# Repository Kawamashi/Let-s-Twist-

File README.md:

# Let's Twist !
## Ergonomic split mechanical keyboard

I'm an [Ergodox keyboard](https://www.ergodox.io/) user. Even if I'm really happy with it, there's room for improvement. *Let's Twist !* is an attempt to gather every brilliant idea I've seen on other ergonomic split keyboards.

First of all, I want to keep some of the Ergodox features :
- the thumb clusters, because it's a great way to lighten the work of the other fingers.
- the columnar staggered arrangement of the keys, because it's way more natural than the traditional row staggered layout.
- the split design, because it allows you to have a very comfortable position.
- programmable with QMK, I don't think I need to explain why…
- 1.5u wide keys on the outer columns, because it's aesthetically pleasing ! 
- wired connectivity, because I don't like to rely on batteries, and because I like my custom cables !

Then, like a lot of people, I find that the thumb clusters of the Ergodox are too far away from the alphas. I saw Mikel Duffy's great [modified Ergodox](https://medium.com/@mikelduffy/hand-wiring-a-modified-ergodox-1adbfc479468), and I want the two main thumb keys to be in the same position.

My project was heavily inspired by Mattia Dal Ben's [Redox keyboard](https://github.com/mattdibi/redox-keyboard). It's really a stunning project. Like him, I want my keyboard to have a reduced size, and to be able to plug either half (or just one of them) to the PC. 

So, here is the layout I get :

The PCB can manage 2 or 3 keys for each of the thumb clusters. The blue keys can be 1u or 1.25u.

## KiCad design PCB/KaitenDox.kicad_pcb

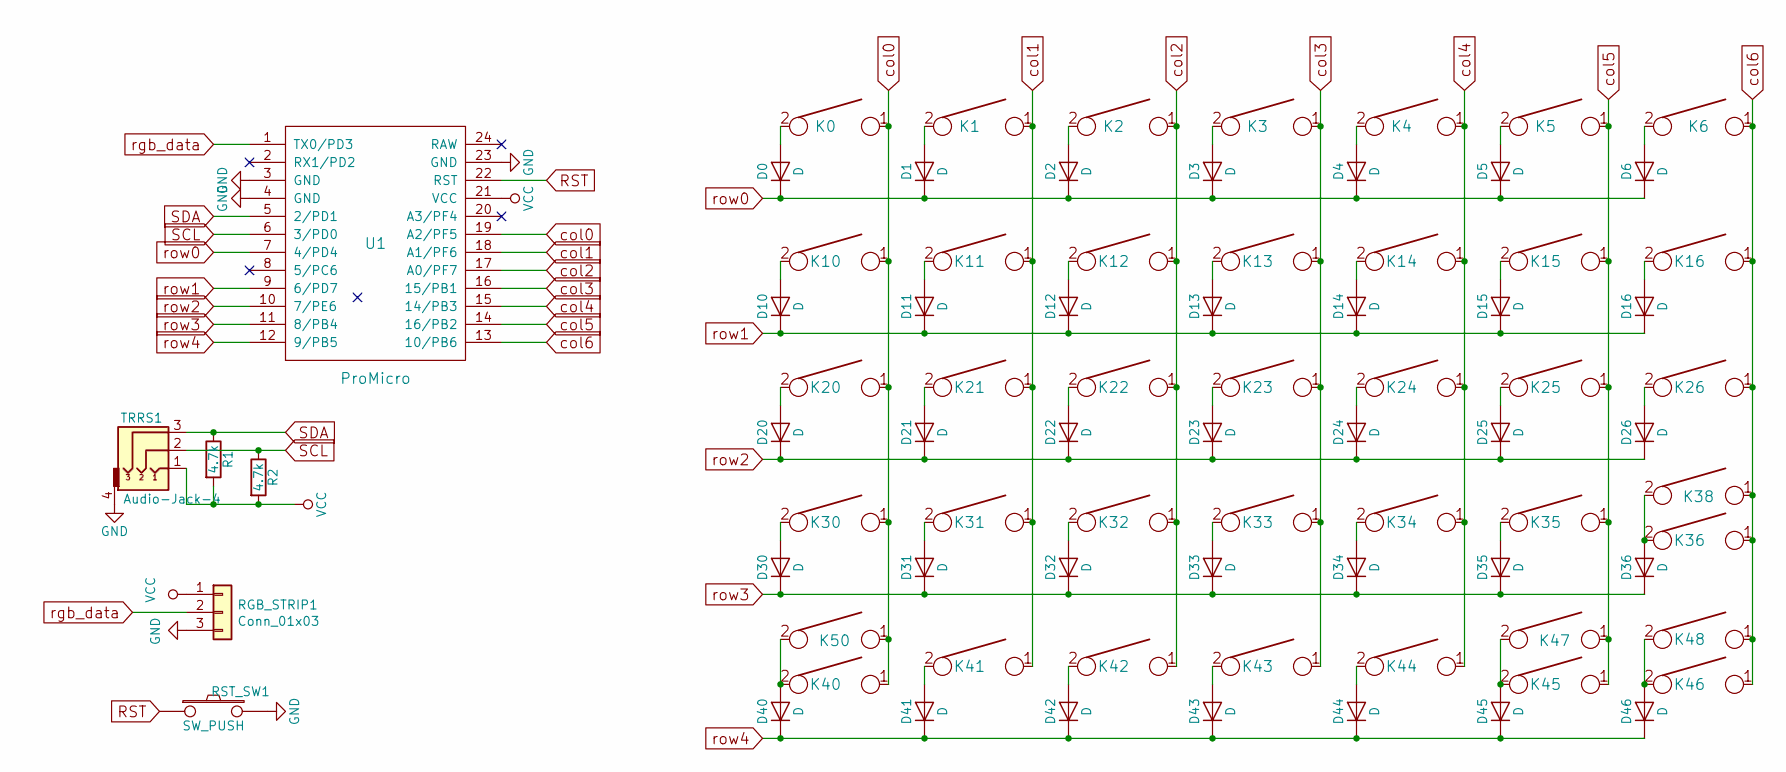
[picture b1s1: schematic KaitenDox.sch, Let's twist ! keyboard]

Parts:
D0, D1, D2, D3, D4, D5, D6, D10, D11, D12, D13, D14, D15, D16, D20, D21, D22, D23, D24, D25, D26, D30, D31, D32, D33, D34, D35, D36, D40, D41, D42, D43, D44, D45, D46: D; Diode-dual
K0, K10, K20, K26, K30: KEYSW; Mx_Alps_150-dualsided
K1, K2, K3, K4, K5, K6, K11, K12, K13, K14, K15, K16, K21, K22, K23, K24, K25, K31, K32, K33, K34, K35, K36, K38, K41, K42, K43, K44, K45, K46, K47, K48, K50: KEYSW; Mx_Alps_100-dualside
K40: KEYSW; Mx_Alps_125-dualside
R1, R2: 4.7k; Resistor-Compact
RGB_STRIP1: Conn_01x03; Pin_Header_Straight_1x03_Pitch2.54mm
RST_SW1: SW_PUSH; SW_PUSH_6mm_h4.3mm
TRRS1: Audio-Jack-4; TRRS-PJ-320A-dual
U1: ProMicro; ArduinoProMicro

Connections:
GND: RGB_STRIP1.3, RST_SW1.2, TRRS1.4, U1.3 (GND), U1.4 (GND), U1.23 (GND)
unnamed: D0.2 (A), K0.2
unnamed: D1.2 (A), K1.2
unnamed: D2.2 (A), K2.2
unnamed: D3.2 (A), K3.2
unnamed: D4.2 (A), K4.2
unnamed: D5.2 (A), K5.2
unnamed: D6.2 (A), K6.2
unnamed: D10.2 (A), K10.2
unnamed: D11.2 (A), K11.2
unnamed: D12.2 (A), K12.2
unnamed: D13.2 (A), K13.2
unnamed: D14.2 (A), K14.2
unnamed: D15.2 (A), K15.2
unnamed: D16.2 (A), K16.2
unnamed: D20.2 (A), K20.2
unnamed: D21.2 (A), K21.2
unnamed: D22.2 (A), K22.2
unnamed: D23.2 (A), K23.2
unnamed: D24.2 (A), K24.2
unnamed: D25.2 (A), K25.2
unnamed: D26.2 (A), K26.2
unnamed: D30.2 (A), K30.2
unnamed: D31.2 (A), K31.2
unnamed: D32.2 (A), K32.2
unnamed: D33.2 (A), K33.2
unnamed: D34.2 (A), K34.2
unnamed: D35.2 (A), K35.2
unnamed: D36.2 (A), K36.2, K38.2
unnamed: D40.2 (A), K40.2, K50.2
unnamed: D41.2 (A), K41.2
unnamed: D42.2 (A), K42.2
unnamed: D43.2 (A), K43.2
unnamed: D44.2 (A), K44.2
unnamed: D45.2 (A), K45.2, K47.2
unnamed: D46.2 (A), K46.2, K48.2
RST: RST_SW1.1, U1.22 (RST)
SCL: R2.1, TRRS1.2, U1.6 (3/PD0)
SDA: R1.1, TRRS1.3, U1.5 (2/PD1)
VCC: R1.2, R2.2, RGB_STRIP1.1, TRRS1.1, U1.21 (VCC)
col0: K0.1, K10.1, K20.1, K30.1, K40.1, K50.1, U1.19 (A2/PF5)
col1: K1.1, K11.1, K21.1, K31.1, K41.1, U1.18 (A1/PF6)
col2: K2.1, K12.1, K22.1, K32.1, K42.1, U1.17 (A0/PF7)
col3: K3.1, K13.1, K23.1, K33.1, K43.1, U1.16 (15/PB1)
col4: K4.1, K14.1, K24.1, K34.1, K44.1, U1.15 (14/PB3)
col5: K5.1, K15.1, K25.1, K35.1, K45.1, K47.1, U1.14 (16/PB2)
col6: K6.1, K16.1, K26.1, K36.1, K38.1, K46.1, K48.1, U1.13 (10/PB6)
rgb_data: RGB_STRIP1.2, U1.1 (TX0/PD3)
row0: D0.1 (K), D1.1 (K), D2.1 (K), D3.1 (K), D4.1 (K), D5.1 (K), D6.1 (K), U1.7 (4/PD4)
row1: D10.1 (K), D11.1 (K), D12.1 (K), D13.1 (K), D14.1 (K), D15.1 (K), D16.1 (K), U1.9 (6/PD7)
row2: D20.1 (K), D21.1 (K), D22.1 (K), D23.1 (K), D24.1 (K), D25.1 (K), D26.1 (K), U1.10 (7/PE6)
row3: D30.1 (K), D31.1 (K), D32.1 (K), D33.1 (K), D34.1 (K), D35.1 (K), D36.1 (K), U1.11 (8/PB4)
row4: D40.1 (K), D41.1 (K), D42.1 (K), D43.1 (K), D44.1 (K), D45.1 (K), D46.1 (K), U1.12 (9/PB5)

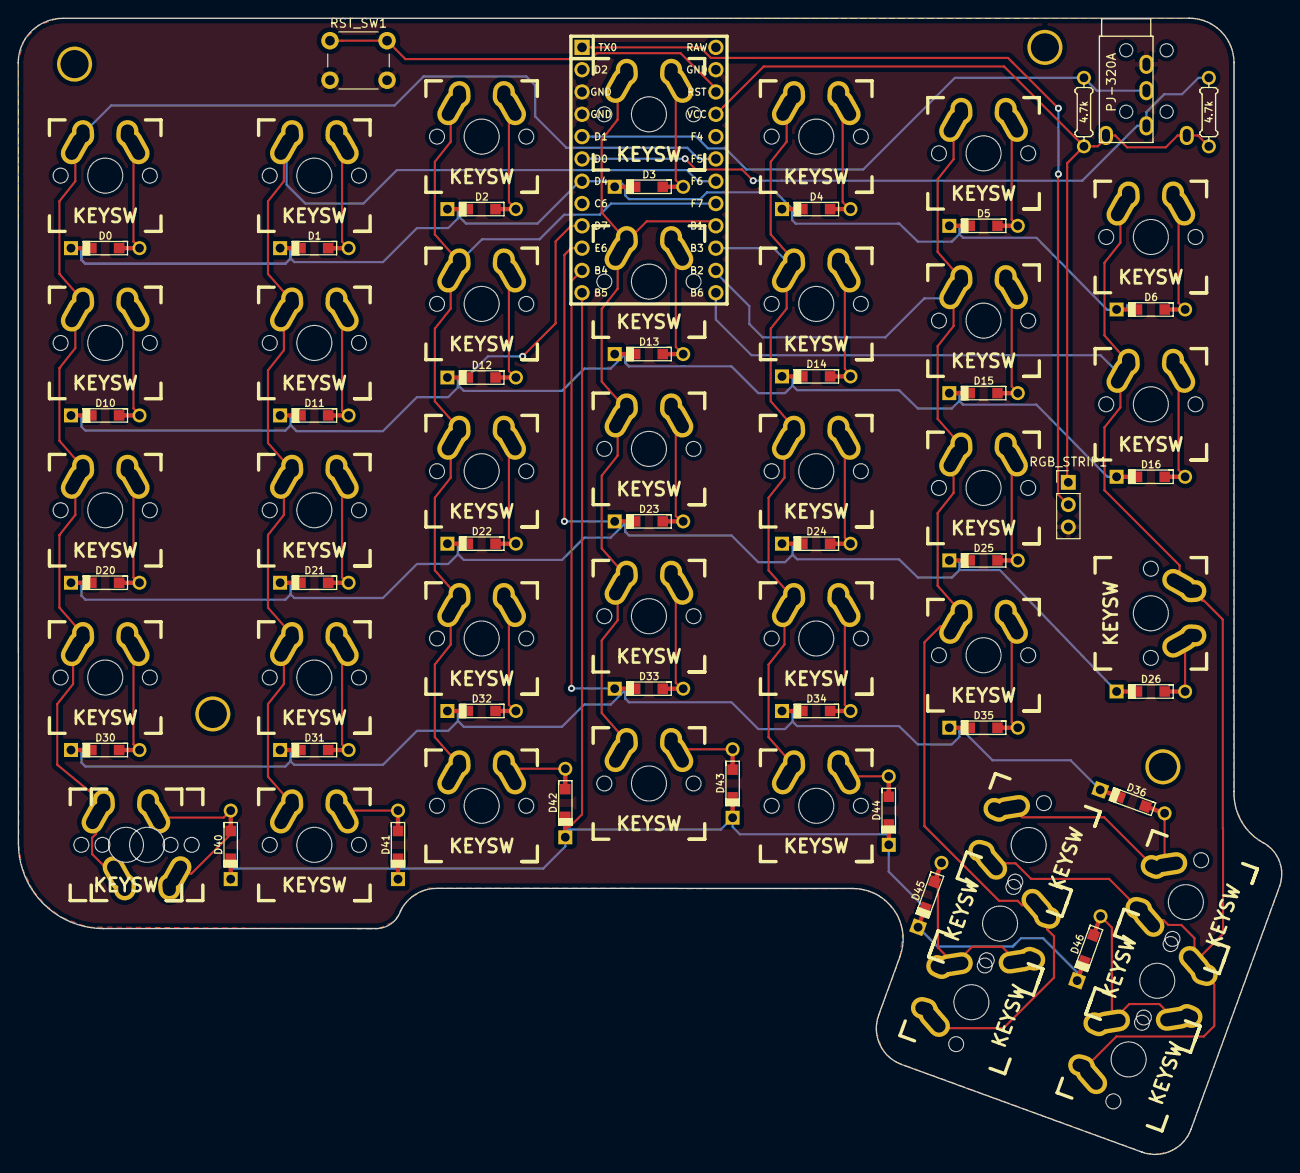
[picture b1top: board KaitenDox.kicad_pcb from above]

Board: 2 copper layers, 143.9 x 129.4 mm, 84 parts (1 on the bottom side), 53 nets.

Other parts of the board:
HOLE_M3, HOLE_M3#2, HOLE_M3#3, HOLE_M3#4: VAL**; HOLE_M3

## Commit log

2019-07-22 Update README.md
    I'm an [Ergodox keyboard](https://www.ergodox.io/) user. Even if I'm really happy with it, there's room for improvement. *Let's Twist !* is an attempt to gather every brilliant idea I've seen on othe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
